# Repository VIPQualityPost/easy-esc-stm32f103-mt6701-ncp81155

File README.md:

# easy-esc-stm32f103-mt6701-ncp81155

Small, closed loop simpleFOC driver board, that can be assembled for &lt;$10 with mostly basic components at LCSC. has support for current sensing and mounting WS2812 RGBLED for indicating, as well as USB C for serial communication and programming. SWD + UART via STLINK 14 pin connector.

The targe for this project was to create an all-in-one simpleFOC board with high resolution magnetic encoder, current sensing, simpleFOC BLDC driver board which can be assembled with top-side only components, 2 layers, mostly basic components from LCSC library, and which can be powered entirely from USB 2.0 specification (500mA) for mostly use with haptic texture type applications. Additionally, it has a compact size of 38x38mm.

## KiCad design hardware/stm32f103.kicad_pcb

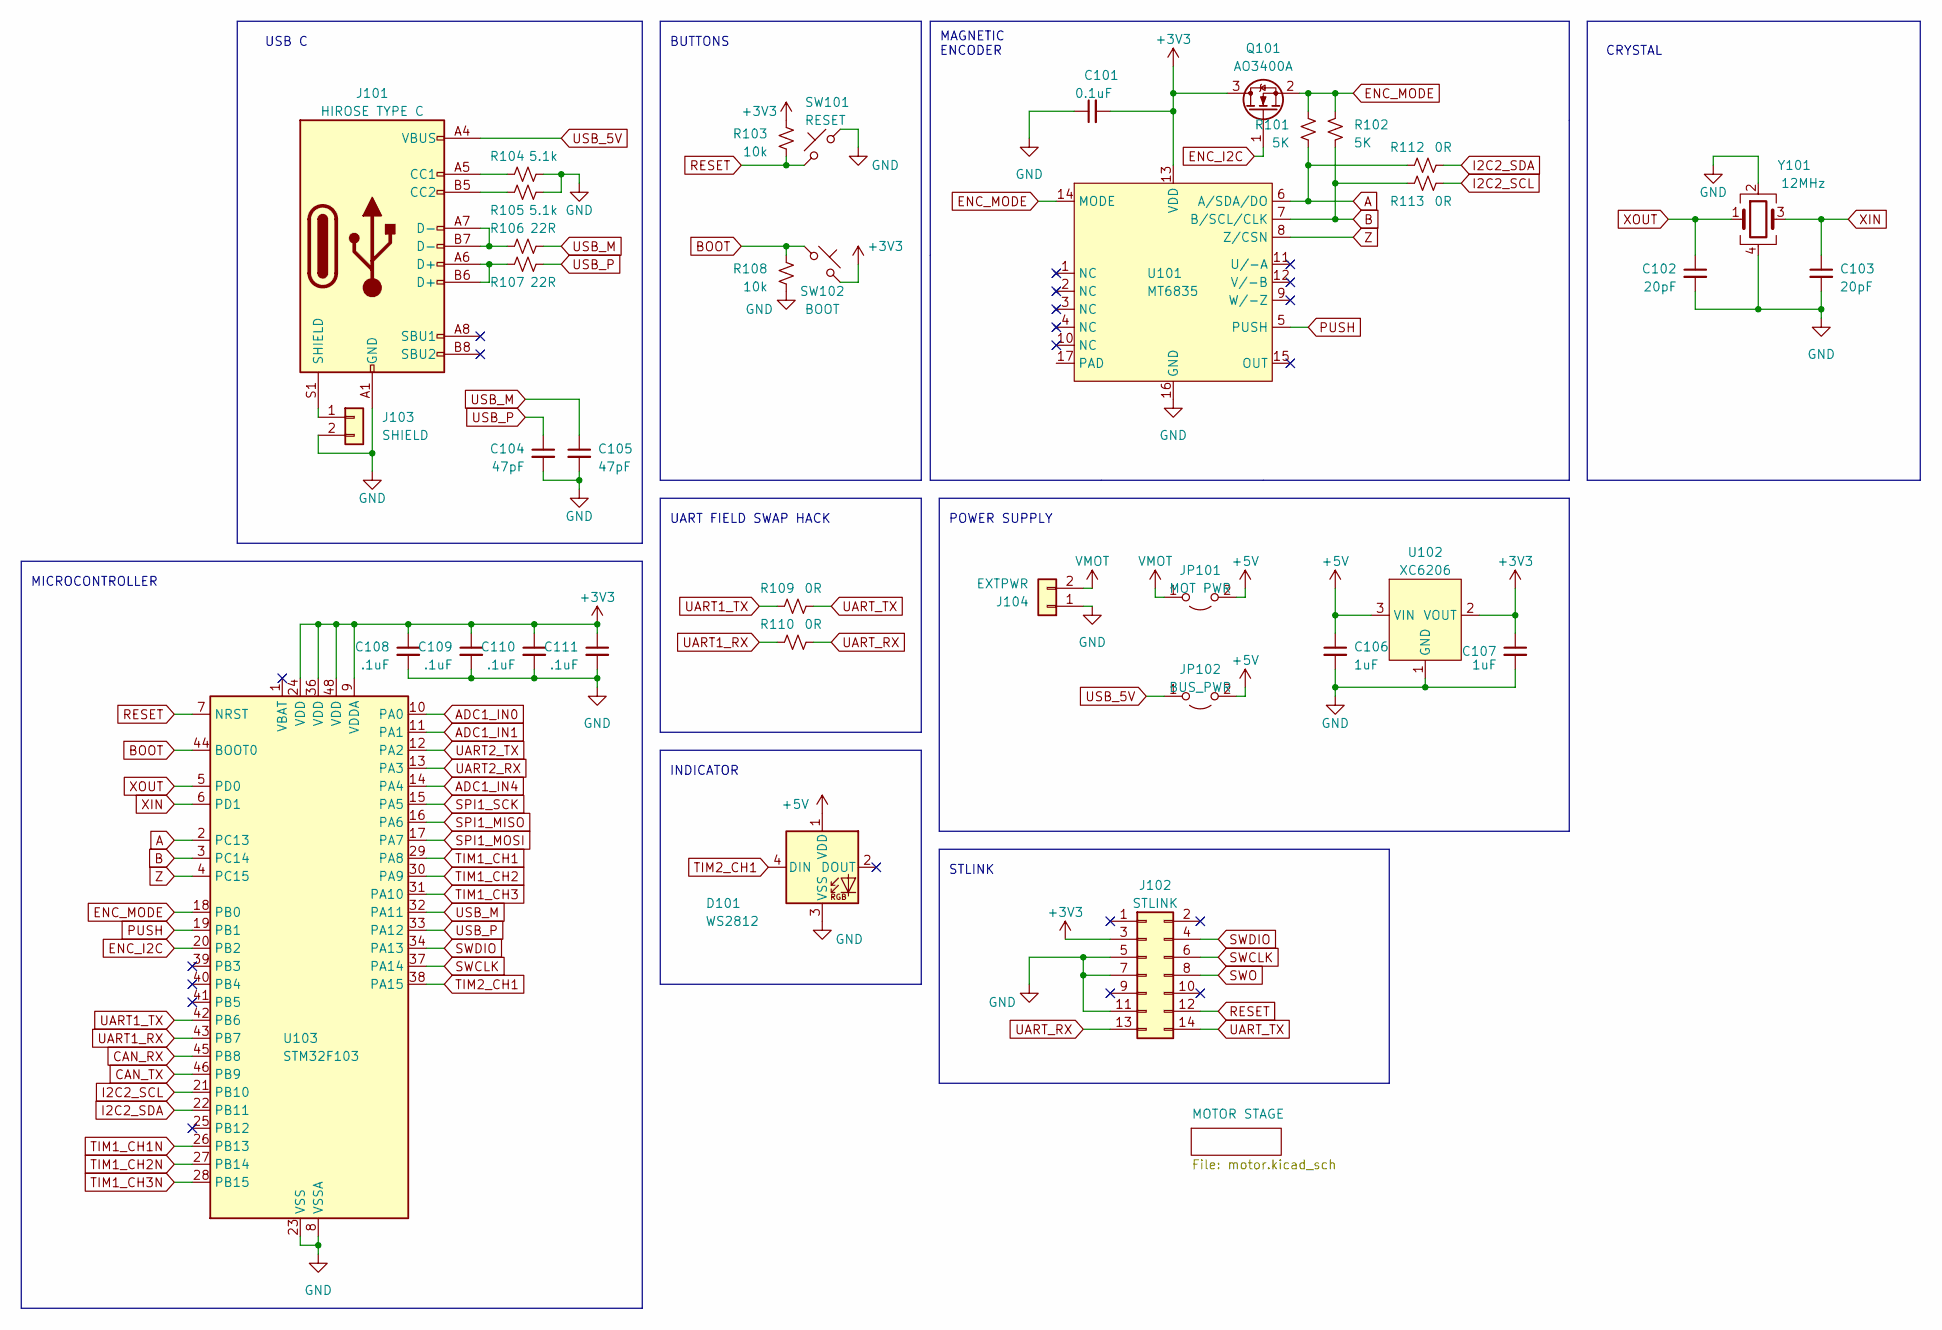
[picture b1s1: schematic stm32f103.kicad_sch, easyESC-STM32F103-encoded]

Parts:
C101: 0.1uF; C_0402_1005Metric
C102, C103: 20pF; C_0402_1005Metric
C104, C105: 47pF; C_0402_1005Metric
C106, C107: 1uF; C_0402_1005Metric
C108, C109, C110, C111: .1uF; C_0402_1005Metric
D101: WS2812; LED_WS2812B_PLCC4_5.0x5.0mm_P3.2mm
J101: HIROSE TYPE C; USB_C_Receptacle_HRO_TYPE-C-31-M-12
J102: STLINK; PinSocket_2x07_P1.27mm_Vertical
J103: SHIELD; SolderJumper-2_P1.3mm_Open_RoundedPad1.0x1.5mm
J104: EXTPWR; JST-XH-edgemount-2p
JP101: MOT PWR; SolderJumper-2_P1.3mm_Open_RoundedPad1.0x1.5mm
JP102: BUS_PWR; SolderJumper-2_P1.3mm_Open_RoundedPad1.0x1.5mm
Q101: AO3400A; SOT-23
R101, R102: 5K; R_0402_1005Metric
R103, R108: 10k; R_0402_1005Metric
R104, R105: 5.1k; R_0402_1005Metric
R106, R107: 22R; R_0402_1005Metric
R109, R110, R112, R113: 0R; R_0402_1005Metric
SW101: RESET; TS-1187A-B-A-B
SW102: BOOT; SolderJumper-2_P1.3mm_Open_TrianglePad1.0x1.5mm
U101: MT6835; QFN-16-1EP_3x3mm_P0.5mm_EP1.7x1.7mm
U102: XC6206; SOT-23
U103: STM32F103; LQFP-48_7x7mm_P0.5mm
Y101: 12MHz; Crystal_SMD_3225-4Pin_3.2x2.5mm

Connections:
+3V3: C101.2, C107.1, C108.1, C109.1, C110.1, C111.1, J102.3, Q101.3 (D), R103.1, SW102.2, U101.13 (VDD), U102.2 (VOUT), U103.9 (VDDA), U103.24 (VDD), U103.36 (VDD), U103.48 (VDD); also elsewhere on the board
+5V: C106.1, D101.1 (VDD), JP101.2 (B), JP102.2 (B), U102.3 (VIN)
A: R101.2, R112.1, U101.6 (A/SDA/DO), U103.2 (PC13)
ADC1_IN0: U103.10 (PA0); also elsewhere on the board
ADC1_IN1: U103.11 (PA1); also elsewhere on the board
ADC1_IN4: U103.14 (PA4); also elsewhere on the board
B: R102.2, R113.1, U101.7 (B/SCL/CLK), U103.3 (PC14)
BOOT: R108.1, SW102.1, U103.44 (BOOT0)
CAN_RX: U103.45 (PB8)
CAN_TX: U103.46 (PB9)
ENC_I2C: Q101.1 (G), U103.20 (PB2)
ENC_MODE: Q101.2 (S), R101.1, R102.1, U101.14 (MODE), U103.18 (PB0)
GND: C101.1, C102.2, C103.2, C104.2, C105.2, C106.2, C107.2, C108.2, C109.2, C110.2, C111.2, D101.3 (VSS), J101.A1 (GND), J101.A12 (GND), J101.B1 (GND), J101.B12 (GND), J102.5, J102.7, J102.11, J103.2, J104.1, R104.2, R105.2, R108.2, SW101.2, U101.16 (GND), U102.1 (GND), U103.8 (VSSA), U103.23 (VSS), U103.35 (VSS), U103.47 (VSS), Y101.2, Y101.4; also elsewhere on the board
I2C2_SCL: R113.2, U103.21 (PB10)
I2C2_SDA: R112.2, U103.22 (PB11)
unnamed: J101.A5 (CC1), R104.1
unnamed: J101.B5 (CC2), R105.1
unnamed: J101.A6 (D+), J101.B6 (D+), R107.1
unnamed: J101.A7 (D-), J101.B7 (D-), R106.1
unnamed: J101.S1 (SHIELD), J103.1
PUSH: U101.5 (PUSH), U103.19 (PB1)
RESET: J102.12, R103.2, SW101.1, U103.7 (NRST)
SPI1_MISO: U103.16 (PA6)
SPI1_MOSI: U103.17 (PA7)
SPI1_SCK: U103.15 (PA5)
SWCLK: J102.6, U103.37 (PA14)
SWDIO: J102.4, U103.34 (PA13)
SWO: J102.8
TIM1_CH1: U103.29 (PA8); also elsewhere on the board
TIM1_CH1N: U103.26 (PB13); also elsewhere on the board
TIM1_CH2: U103.30 (PA9); also elsewhere on the board
TIM1_CH2N: U103.27 (PB14); also elsewhere on the board
TIM1_CH3: U103.31 (PA10); also elsewhere on the board
TIM1_CH3N: U103.28 (PB15); also elsewhere on the board
TIM2_CH1: D101.4 (DIN), U103.38 (PA15)
UART1_RX: R110.1, U103.43 (PB7)
UART1_TX: R109.1, U103.42 (PB6)
UART2_RX: U103.13 (PA3)
UART2_TX: U103.12 (PA2)
UART_RX: J102.13, R110.2
UART_TX: J102.14, R109.2
USB_5V: J101.A4 (VBUS), J101.A9 (VBUS), J101.B4 (VBUS), J101.B9 (VBUS), JP102.1 (A)
USB_M: C105.1, R106.2, U103.32 (PA11)
USB_P: C104.1, R107.2, U103.33 (PA12)
VMOT: J104.2, JP101.1 (A); also elsewhere on the board
XIN: C103.1, U103.6 (PD1), Y101.3
XOUT: C102.1, U103.5 (PD0), Y101.1
Z: U101.8 (Z/CSN), U103.4 (PC15)

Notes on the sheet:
INDICATOR
USB C
POWER SUPPLY
STLINK
MAGNETIC ENCODER
BUTTONS
UART FIELD SWAP HACK
MICROCONTROLLER
CRYSTAL

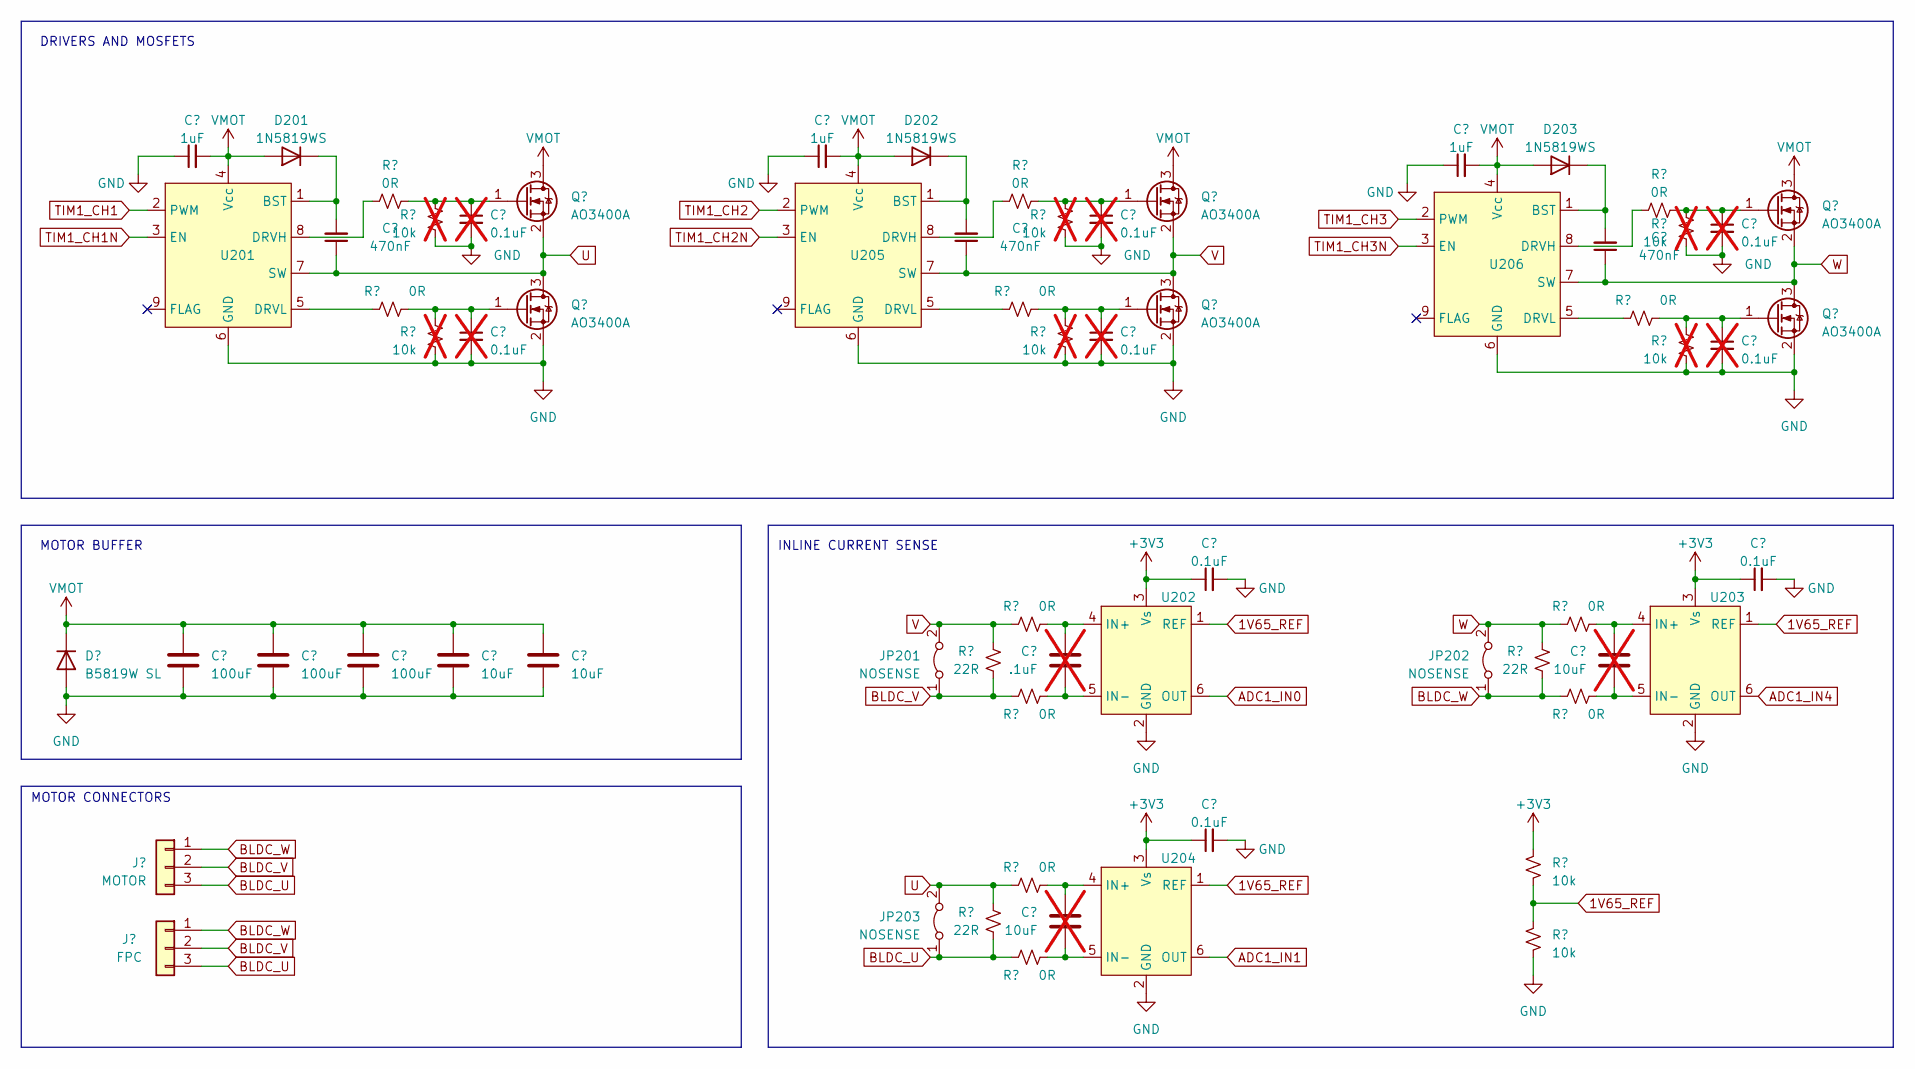
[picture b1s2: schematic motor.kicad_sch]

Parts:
C201, C206, C210: 1uF; C_0402_1005Metric
C202, C203, C204, C207, C208, C209: 0.1uF; C_0402_1005Metric; not fitted
C205, C222, C223: 470nF; C_0402_1005Metric
C211, C212, C218: 0.1uF; C_0402_1005Metric
C213, C220, C221: 100uF; C_1206_3216Metric
C214, C215: 10uF; C_0402_1005Metric
C216: .1uF; C_0402_1005Metric; not fitted
C217, C219: 10uF; C_0402_1005Metric; not fitted
D201, D202, D203: 1N5819WS; D_SOD-323
D204: B5819W SL; D_SOD-123
J201: MOTOR; PinHeader_1x03_P1.27mm_Vertical
J202: FPC; FPC-SMD_3P-P1.00_HDGC_1.0K-LS-3PWB-BOTTOMCONTACT
JP201, JP202, JP203: NOSENSE; SolderJumper-2_P1.3mm_Open_TrianglePad1.0x1.5mm
Q201, Q202, Q203, Q204, Q205, Q206: AO3400A; SOT-23
R201, R202, R203, R207, R208, R209, R213, R214, R217, R218, R220, R223: 0R; R_0402_1005Metric
R204, R205, R206, R210, R211, R212: 10k; R_0402_1005Metric; not fitted
R215, R216, R221: 22R; R_1206_3216Metric
R219, R222: 10k; R_0402_1005Metric
U201, U205, U206: DFN-8-1EP_3x3mm_P0.5mm_EP1.65x2.38mm
U202, U203, U204: SOT-363_SC-70-6

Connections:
1V65_REF: R219.2, R222.1, U202.1 (REF), U203.1 (REF), U204.1 (REF)
+3V3: C211.1, C212.1, C218.1, R219.1, U202.3 (Vs), U203.3 (Vs), U204.3 (Vs); also elsewhere on the board
ADC1_IN0: U202.6 (OUT); also elsewhere on the board
ADC1_IN1: U204.6 (OUT); also elsewhere on the board
ADC1_IN4: U203.6 (OUT); also elsewhere on the board
BLDC_U: J201.3, J202.3, JP203.1 (A), R221.1, R223.1
BLDC_V: J201.2, J202.2, JP201.1 (A), R215.1, R217.1
BLDC_W: J201.1, J202.1, JP202.1 (A), R216.1, R218.1
GND: C201.1, C202.2, C203.2, C204.2, C206.1, C207.2, C208.2, C209.2, C210.1, C211.2, C212.2, C213.2, C214.2, C215.2, C218.2, C220.2, C221.2, D204.2 (A), Q204.2 (S), Q205.2 (S), Q206.2 (S), R204.2, R205.2, R206.2, R210.2, R211.2, R212.2, R222.2, U201.6 (GND), U202.2 (GND), U203.2 (GND), U204.2 (GND), U205.6 (GND), U206.6 (GND); also elsewhere on the board
unnamed: C205.2, D201.1 (K), U201.1 (BST)
unnamed: C223.2, D202.1 (K), U205.1 (BST)
unnamed: C222.2, D203.1 (K), U206.1 (BST)
unnamed: C202.1, Q201.1 (G), R201.2, R204.1
unnamed: C203.1, Q202.1 (G), R202.2, R205.1
unnamed: C204.1, Q203.1 (G), R203.2, R206.1
unnamed: C207.1, Q204.1 (G), R207.2, R210.1
unnamed: C208.1, Q205.1 (G), R208.2, R211.1
unnamed: C209.1, Q206.1 (G), R209.2, R212.1
unnamed: R201.1, U201.8 (DRVH)
unnamed: R207.1, U201.5 (DRVL)
unnamed: C216.1, R213.2, U202.4 (IN+)
unnamed: C216.2, R217.2, U202.5 (IN-)
unnamed: C217.1, R214.2, U203.4 (IN+)
unnamed: C217.2, R218.2, U203.5 (IN-)
unnamed: C219.1, R220.2, U204.4 (IN+)
unnamed: C219.2, R223.2, U204.5 (IN-)
unnamed: R202.1, U205.8 (DRVH)
unnamed: R208.1, U205.5 (DRVL)
unnamed: R203.1, U206.8 (DRVH)
unnamed: R209.1, U206.5 (DRVL)
TIM1_CH1: U201.2 (PWM); also elsewhere on the board
TIM1_CH1N: U201.3 (EN); also elsewhere on the board
TIM1_CH2: U205.2 (PWM); also elsewhere on the board
TIM1_CH2N: U205.3 (EN); also elsewhere on the board
TIM1_CH3: U206.2 (PWM); also elsewhere on the board
TIM1_CH3N: U206.3 (EN); also elsewhere on the board
U: C205.1, JP203.2 (B), Q201.2 (S), Q204.3 (D), R220.1, R221.2, U201.7 (SW)
V: C223.1, JP201.2 (B), Q202.2 (S), Q205.3 (D), R213.1, R215.2, U205.7 (SW)
VMOT: C201.2, C206.2, C210.2, C213.1, C214.1, C215.1, C220.1, C221.1, D201.2 (A), D202.2 (A), D203.2 (A), D204.1 (K), Q201.3 (D), Q202.3 (D), Q203.3 (D), U201.4 (Vcc), U205.4 (Vcc), U206.4 (Vcc); also elsewhere on the board
W: C222.1, JP202.2 (B), Q203.2 (S), Q206.3 (D), R214.1, R216.2, U206.7 (SW)

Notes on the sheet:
MOTOR BUFFER
MOTOR CONNECTORS
DRIVERS AND MOSFETS
INLINE CURRENT SENSE

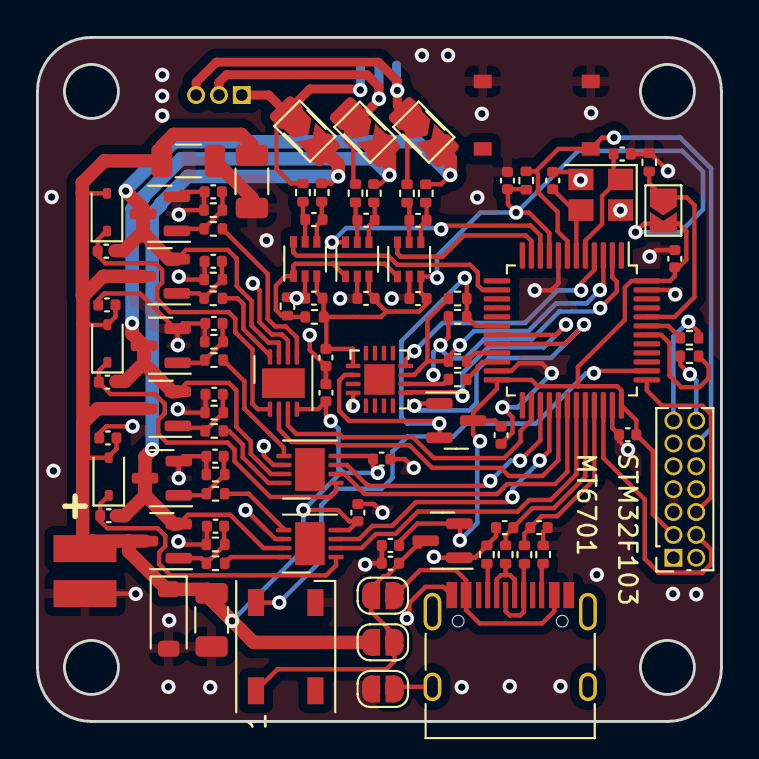
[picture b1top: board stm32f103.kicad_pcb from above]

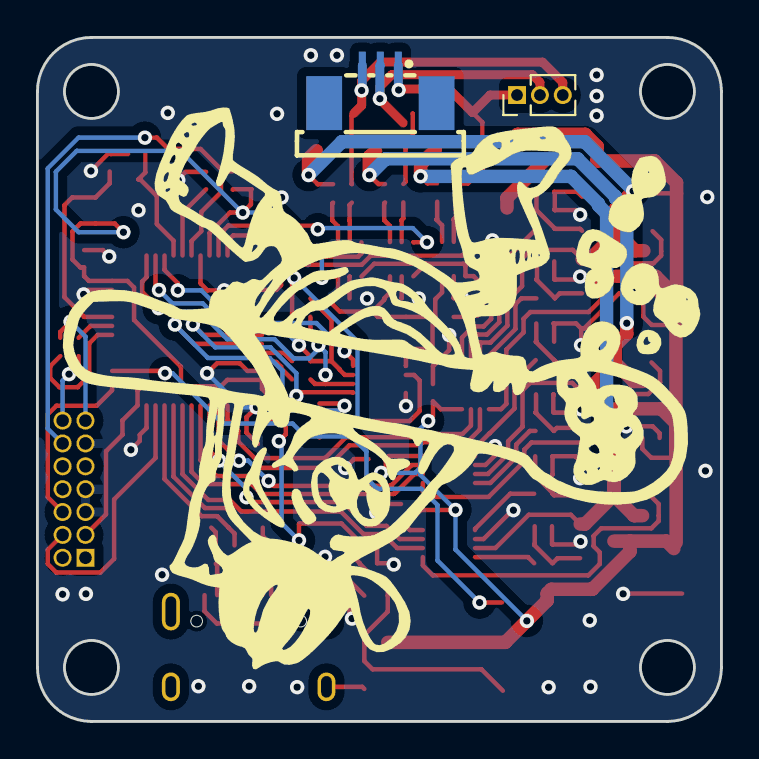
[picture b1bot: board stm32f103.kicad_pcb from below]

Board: 2 copper layers, 38.0 x 38.0 mm, 104 parts (2 on the bottom side), 68 nets.

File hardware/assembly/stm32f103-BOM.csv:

Comment,Designator,Footprint,LCSC
5K,"R102,R101",0402_R,
22R,"R106,R107",0402_R,
1uF,"C206,C201,C210,C107,C106",0402_C,
WS2812,D101,SMD_5050,
0R,"R209,R207,R223,R203,R201,R217,R213,R202,R113,R220,R218,R208,R112,R214,R110,R109",0402_R,
NCP81155,"U205,U201,U206",DFN-8_3x3mm,C173765
0.1uF,"C101,C212,C218,C211,C109,C111,C110,C108",0402_C,
1N5819WS,"D201,D202,D203",D_SOD-323,C191023
22R,"R215,R216,R221",1206_R,
47pF,"C105,C104",0402_C,
10k,"R219,R108,R103,R222",0402_R,
RESET,SW101,TS-1187A-B-A-B,C318884
LT199,"U204,U203,U202",SOT-363_SC-70-6,C2888104
10uF,"C214,C215",0402_C,
AO3400A,"Q201,Q205,Q203,Q202,Q101,Q206,Q204",SOT-23,C20917
470nF,"C222,C205,C223",0402_C,
5.1k,"R105,R104",0402_R,
20pF,"C102,C103",0402_C,
12MHz,Y101,Crystal_SMD_3225,
HIROSE TYPE C ,J101,HRO_TYPE-C-31-M-12,C165948
100uF,"C221,C220,C213",1206_C,
STM32F103,U103,LQFP-48_7x7mm,C8734
XC6206,U102,SOT-23,C5446
B5819W SL,D204,D_SOD-123,C8598
MT6701,U101,QFN-16-1EP_3x3mm,C2913974

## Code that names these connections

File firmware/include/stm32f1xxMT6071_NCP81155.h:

#pragma once

// encoder interface
#define ENC_A PC13
#define ENC_B PC14
#define ENC_Z PC15

#define ENC_PUSH PB1
#define ENC_MODE PB0
#define ENC_I2C_EN PB2

// mosfet driver pins
// allow for dir switch to match encoder on build flag MOTOR_CW

#define PWM_U PA9
#define EN_U PB14
#define PWM_V PA8
#define EN_V PB13  
#define PWM_W PA10
#define EN_W PB15 

// current sensing pins
#define CUR_U PA1
#define CUR_V PA0
#define CUR_W PA4

// ws2812E
#define RGB_LED PA15

// SPI1
#define SPI1_MOSI PA7
#define SPI1_MISO PA6
#define SPI1_SCLK PA5

// UART1
#define UART1_TX PB6
#define UART1_RX PB7

// CANBUS1
#define CAN_TX PB9
#define CAN_RX PB8 

// I2C2
#define I2C2_SDA PB11
#define I2C2_SCL PB10

// UART2
#define UART2_TX PA2
#define UART2_RX PA3

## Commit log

2023-03-21 fix render image
2023-03-21 add schematic pdf
2023-03-29 add in platformio configuration
2023-03-29 serial bugs?
2023-03-29 try to use usb serial
2023-03-29 tidy up
2023-03-29 change title image
2023-03-30 get USB serial working with add 1.5k pullup on D+
2023-03-31 start working on closed loop
2023-04-02 get closed loop working, fix i2c driver for mt6701
2023-04-02 get commander interface working
2023-04-11 Auto-commit Tue Apr 11 10:47:16 EDT 2023
2023-04-30 Auto-commit Sun Apr 30 10:54:41 EDT 2023
2023-05-12 add dalton
2023-05-14 Auto-commit Sun May 14 18:30:04 EDT 2023
2023-05-29 remove system specific files PlatformIO creates files in the .pio folder along with c_cpp_properties.json and launch.json when it builds a project. These are system specific and probably shouldn't be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
2023-05-29 fix readme formatting
2023-06-25 I deleted lots of old hardware parameters that are not valid for this board
2023-06-25 remove serialUsb from useMonitoring call
2023-06-25 add serial to commander
2023-06-25 Revert to working firmware, clean up gitignore, remove unused library from platformio.ini
2023-06-25 stupid stupid stupid
2023-06-25 i dont know
2023-06-25 Clean up main.cpp
2023-06-25 Remove unused library from pio.ini
2023-06-25 remove vestigal folder
2023-06-25 tune PID params
2023-06-26 try out electron demo
2023-06-27 fix PID gains
2023-07-01 starter electron app
2023-07-01 setup Home component
2023-07-01 replace ReactDOM with createRoot to fit React 18 spec
2023-07-01 add serial port types
2023-07-02 setup serial device settings on session
2023-07-02 displays serial output when connected to a port
2023-07-02 add readme
2023-07-03 Remove kicad_pcb from gitgnore
2023-07-03 Update and fix gitignores
2023-07-03 try to reduce flash size
2023-07-03 Fix build issues from updated STSTM32 platform
2023-07-03 Tune PIDs
